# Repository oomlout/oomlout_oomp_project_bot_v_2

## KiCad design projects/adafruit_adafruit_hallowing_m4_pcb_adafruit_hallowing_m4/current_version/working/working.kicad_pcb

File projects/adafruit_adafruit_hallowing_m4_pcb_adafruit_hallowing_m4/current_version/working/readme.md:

# adafruit_hallowing_m4_pcb
 
## summary 
* id: adafruit_adafruit_hallowing_m4_pcb_adafruit_hallowing_m4
* user: adafruit
* name: adafruit_hallowing_m4_pcb
* board: adafruit_hallowing_m4
* repo: https://github.com/adafruit/Adafruit-Hallowing-M4-PCB

* src_file_repo_sch: 
* src_file_repo_sch_link: https://github.com/adafruit/Adafruit-Hallowing-M4-PCB/tree/master/
* full details link: https://github.com/oomlout/oomlout_oomp_project_bot_v_2/tree/main/projects/adafruit_adafruit_hallowing_m4_pcb_adafruit_hallowing_m4/current_version/working  

## schematic  
  
[schematic (pdf)](working_schematic.pdf) 

## pcb  

[board (pdf)](working.pdf)  

## working_bom
| Id | Designator | Footprint | Quantity | Designation | Supplier and ref |  | None | 
| --- | --- | --- | --- | --- | --- | --- | --- | 
| 1 | @HOLE0,@HOLE2,@HOLE3,@HOLE1 |  | 4 |  |  |  | [''] | 
| 2 | C28,C23,C32,C29,C12,C27,C24 | 0603-NO | 7 | 1uF |  |  | [''] | 
| 3 | C18,C30,C21,C26,C19 | 0805-NO | 5 | 10uF |  |  | [''] | 
| 4 | TP3,TP29 | PCB_ALLI_LONG | 2 | SEWTAP_ALLILONG |  |  | [''] | 
| 5 | TP6,TP7 | TESTPOINT_ROUND_1.5MM | 2 |  |  |  | [''] | 
| 6 | U$32,U$31 | MOUNTINGHOLE_2.5_PLATED | 2 | MOUNTINGHOLE2.5 |  |  | [''] | 
| 7 | U$59 | 53398-0271 | 1 | CON_MOLEX_2P |  |  | [''] | 
| 8 | R5,R2,R1,R4 | 0603-NO | 4 | 1M |  |  | [''] | 
| 9 | U$1 | HALLOWINGM4_BACK | 1 |  |  |  | [''] | 
| 10 | C31,C25 | 0603-NO | 2 | 0.1uF |  |  | [''] | 
| 11 | R25,R26 | 0603-NO | 2 | 100K |  |  | [''] | 
| 12 | CHG1 | CHIPLED_0805_NOOUTLINE | 1 | ORANGE |  |  | [''] | 
| 13 | L1 | CHIPLED_0805_NOOUTLINE | 1 | RED |  |  | [''] | 
| 14 | SW3 | BTN_KMR2_4.6X2.8 | 1 | SPST_TACT-EVQQ2 |  |  | [''] | 
| 15 | R11,R17,R18 | 0603-NO | 3 | 1K |  |  | [''] | 
| 16 | R24 | 0603-NO | 1 | 47K |  |  | [''] | 
| 17 | C33,C22,C16,C17 | 0805-NO | 4 | 10ÂµF |  |  | [''] | 
| 18 | R23 | 0603-NO | 1 | 10 |  |  | [''] | 
| 19 | Q6,Q5 | SOT23-R | 2 | DMG3405 |  |  | [''] | 
| 20 | LED3,LED2,LED4,LED1 | WS2812B_4020 | 4 | WS2812B_4020 |  |  | [''] | 
| 21 | R19,R3,R20 | 0603-NO | 3 | 10K |  |  | [''] | 
| 22 | U7 | SOT23-5 | 1 | MCP73831T-2ACI/OT |  |  | [''] | 
| 23 | U9 | SOIC8_208MIL | 1 | GD25Q64 |  |  | [''] | 
| 24 | U$34,U$35 | FIDUCIAL_1MM | 2 | FIDUCIAL_1MM |  |  | [''] | 
| 25 | MS2 | FEATHERWING_SMT_NOHOLES | 1 | FEATHERWING_SMTDUALNOHOLES |  |  | [''] | 
| 26 | TP28,TP4 | PCB_ALLI | 2 | SEWTAPPCB_ALLIGATOR |  |  | [''] | 
| 27 | U4 | ALS-PT26-21C | 1 | ALS-PT21 |  |  | [''] | 
| 28 | IC3 | SOT23-6 | 1 | PAM8301 |  |  | [''] | 
| 29 | R27 | RESPACK_4X0603 | 1 | 10K |  |  | [''] | 
| 30 | Q7 | SOT363 | 1 | BSS138 |  |  | [''] | 
| 31 | Q4 | SOT23-WIDE | 1 | BSS138 |  |  | [''] | 
| 32 | I2C1 | JSTPH4 | 1 | JST PH 4 |  |  | [''] | 
| 33 | SJ2 | SOLDERJUMPER_2WAY_OPEN_NOPASTE | 1 |  |  |  | [''] | 
| 34 | U6 | SOT23-5 | 1 | AP2112-3.3 |  |  | [''] | 
| 35 | D6,D5 | SOD-323 | 2 | 3.6V |  |  | [''] | 
| 36 | FB1 | 0805-NO | 1 | Ferrite |  |  | [''] | 
| 37 | R14 | 0603-NO | 1 | 4.7K |  |  | [''] | 
| 38 | IC2 | LGA12_2X2MM | 1 | MSA301 |  |  | [''] | 
| 39 | R10 | 0603-NO | 1 | 2.2K |  |  | [''] | 
| 40 | NEOPIX1,SENSE1 | JSTPH3 | 2 | JST PH 3 |  |  | [''] | 
| 41 | D3 | SOD-123 | 1 | MBR0540 |  |  | [''] | 
| 42 | U$63 | PQFN64-1 | 1 | ATSAMD51J19 |  |  | [''] | 
| 43 | SW1 | EG1390 | 1 |  |  |  | [''] | 
| 44 | R15 | RESPACK_4X0603 | 1 | 100K |  |  | [''] | 
| 45 | X2 | 4UCONN_20329_V2 | 1 | microUSB |  |  | [''] | 
| 46 | X4 | JSTPH2 | 1 | JSTPH |  |  | [''] | 
| 47 | U$79 | PCBFEAT-REV-040 | 1 |  |  |  | [''] | 
| 48 | TFT1 | TFT_1.54IN_240X240_HANDSOLDER | 1 | DISP_LCD_GENERIC_SPITFT_VDDIO_1.54_240X240_HANDSOLDER |  |  | [''] | 
| 49 | U$2 | HALLOWINGM4_FRONT | 1 |  |  |  | [''] | 

## bom_schematic
| Ref | Qnty | Value | Cmp name | Footprint | Description | Vendor | DNP | 
| --- | --- | --- | --- | --- | --- | --- | --- | 
| C12, C23, C24, C27, C28, C29, C32 | 7 | 1uF | CAP_CERAMIC0603_NO | working:0603-NO |  |  |  | 
| C16, C17, C22, C33 | 4 | 10ÂµF | CAP_CERAMIC0805-NOOUTLINE | working:0805-NO |  |  |  | 
| C18, C19, C21, C26, C30 | 5 | 10uF | CAP_CERAMIC0805-NOOUTLINE | working:0805-NO |  |  |  | 
| C25, C31 | 2 | 0.1uF | CAP_CERAMIC0603_NO | working:0603-NO |  |  |  | 
| CHG1 | 1 | ORANGE | LED0805_NOOUTLINE | working:CHIPLED_0805_NOOUTLINE |  |  |  | 
| D3 | 1 | MBR0540 | DIODE-SCHOTTKYSOD-123 | working:SOD-123 |  |  |  | 
| D5, D6 | 2 | 3.6V | DIODE-ZENERSOD323 | working:SOD-323 |  |  |  | 
| FB1 | 1 | Ferrite | FERRITE-0805NO | working:0805-NO |  |  |  | 
| I2C1 | 1 | STEMMA_I2C_RASMT | STEMMA_I2C_RASMT | working:JSTPH4 |  |  |  | 
| IC2 | 1 | MSA301 | MSA301 | working:LGA12_2X2MM |  |  |  | 
| IC3 | 1 | PAM8301 | PAM8301 | working:SOT23-6 |  |  |  | 
| L1 | 1 | RED | LED0805_NOOUTLINE | working:CHIPLED_0805_NOOUTLINE |  |  |  | 
| LED1, LED2, LED3, LED4 | 4 | WS2812B_4020 | WS2812B_4020 | working:WS2812B_4020 |  |  |  | 
| MS2 | 1 | FEATHERWING_SMTDUALNOHOLES | FEATHERWING_SMTDUALNOHOLES | working:FEATHERWING_SMT_NOHOLES |  |  |  | 
| NEOPIX1 | 1 | JST PH 3 | CON_JST_PH_3PIN | working:JSTPH3 |  |  |  | 
| Q4 | 1 | BSS138 | MOSFET-NWIDE | working:SOT23-WIDE |  |  |  | 
| Q5, Q6 | 2 | DMG3405 | MOSFET-P | working:SOT23-R |  |  |  | 
| Q7 | 1 | BSS138 | MOSFET-N_DUAL | working:SOT363 |  |  |  | 
| R1, R2, R4, R5 | 4 | 1M | RESISTOR_0603_NOOUT | working:0603-NO |  |  |  | 
| R3, R19, R20 | 3 | 10K | RESISTOR_0603_NOOUT | working:0603-NO |  |  |  | 
| R10 | 1 | 2.2K | RESISTOR_0603_NOOUT | working:0603-NO |  |  |  | 
| R11, R17, R18 | 3 | 1K | RESISTOR_0603_NOOUT | working:0603-NO |  |  |  | 
| R14 | 1 | 4.7K | RESISTOR_0603_NOOUT | working:0603-NO |  |  |  | 
| R15 | 1 | 100K | RESISTOR_4PACK | working:RESPACK_4X0603 |  |  |  | 
| R23 | 1 | 10 | RESISTOR_0603_NOOUT | working:0603-NO |  |  |  | 
| R24 | 1 | 47K | RESISTOR_0603_NOOUT | working:0603-NO |  |  |  | 
| R25, R26 | 2 | 100K | RESISTOR_0603_NOOUT | working:0603-NO |  |  |  | 
| R27 | 1 | 10K | RESISTOR_4PACK | working:RESPACK_4X0603 |  |  |  | 
| SENSE1 | 1 | JST PH 3 | CON_JST_PH_3PIN | working:JSTPH3 |  |  |  | 
| SJ2 | 1 | SOLDERJUMPER_2WAY | SOLDERJUMPER_2WAY | working:SOLDERJUMPER_2WAY_OPEN_NOPASTE |  |  |  | 
| SW1 | 1 | SWITCH_DPDTEG1390 | SWITCH_DPDTEG1390 | working:EG1390 |  |  |  | 
| SW3 | 1 | SPST_TACT-EVQQ2 | SWITCH_TACT_SMT4.6X2.8 | working:BTN_KMR2_4.6X2.8 |  |  |  | 
| TFT1 | 1 | DISP_LCD_GENERIC_SPITFT_VDDIO_1.54_240X240_HANDSOLDER | DISP_LCD_GENERIC_SPITFT_VDDIO_1.54_240X240_HANDSOLDER | working:TFT_1.54IN_240X240_HANDSOLDER |  |  |  | 
| TP3, TP29 | 2 | SEWTAP_ALLILONG | SEWTAP_ALLILONG | working:PCB_ALLI_LONG |  |  |  | 
| TP4, TP28 | 2 | SEWTAPPCB_ALLIGATOR | SEWTAPPCB_ALLIGATOR | working:PCB_ALLI |  |  |  | 
| TP6, TP7 | 2 | TESTPOINTROUND1.5MM | TESTPOINTROUND1.5MM | working:TESTPOINT_ROUND_1.5MM |  |  |  | 
| U4 | 1 | ALS-PT21 | PHOTOTRANSISTOR_PT26-21C | working:ALS-PT26-21C |  |  |  | 
| U6 | 1 | AP2112-3.3 | VREG_SOT23-5 | working:SOT23-5 |  |  |  | 
| U7 | 1 | MCP73831T-2ACI/OT | MCP73831/2 | working:SOT23-5 |  |  |  | 
| U9 | 1 | GD25Q64 | SPIFLASH_8PIN208MIL | working:SOIC8_208MIL |  |  |  | 
| U$31, U$32 | 2 | MOUNTINGHOLE2.5 | MOUNTINGHOLE2.5 | working:MOUNTINGHOLE_2.5_PLATED |  |  |  | 
| U$34, U$35 | 2 | FIDUCIAL_1MM | FIDUCIAL_1MM | working:FIDUCIAL_1MM |  |  |  | 
| U$59 | 1 | CON_MOLEX_2P | CON_MOLEX_2P | working:53398-0271 |  |  |  | 
| U$63 | 1 | ATSAMD51J | ATSAMD51J | working:PQFN64-1 |  |  |  | 
| X2 | 1 | microUSB | USB_MICRO_20329_V2 | working:4UCONN_20329_V2 |  |  |  | 
| X4 | 1 | JSTPH | CON_JST_PH_2PIN | working:JSTPH2 |  |  |  | 

## mounting_holes
| x | y | package | value | ref | size | 
| --- | --- | --- | --- | --- | --- | 
| 17.78 | 0.0 | MOUNTINGHOLE_2.5_PLATED | MOUNTINGHOLE2.5 | U$31 | m3 | 
| 0.0 | 0.0 | MOUNTINGHOLE_2.5_PLATED | MOUNTINGHOLE2.5 | U$32 | m3 |

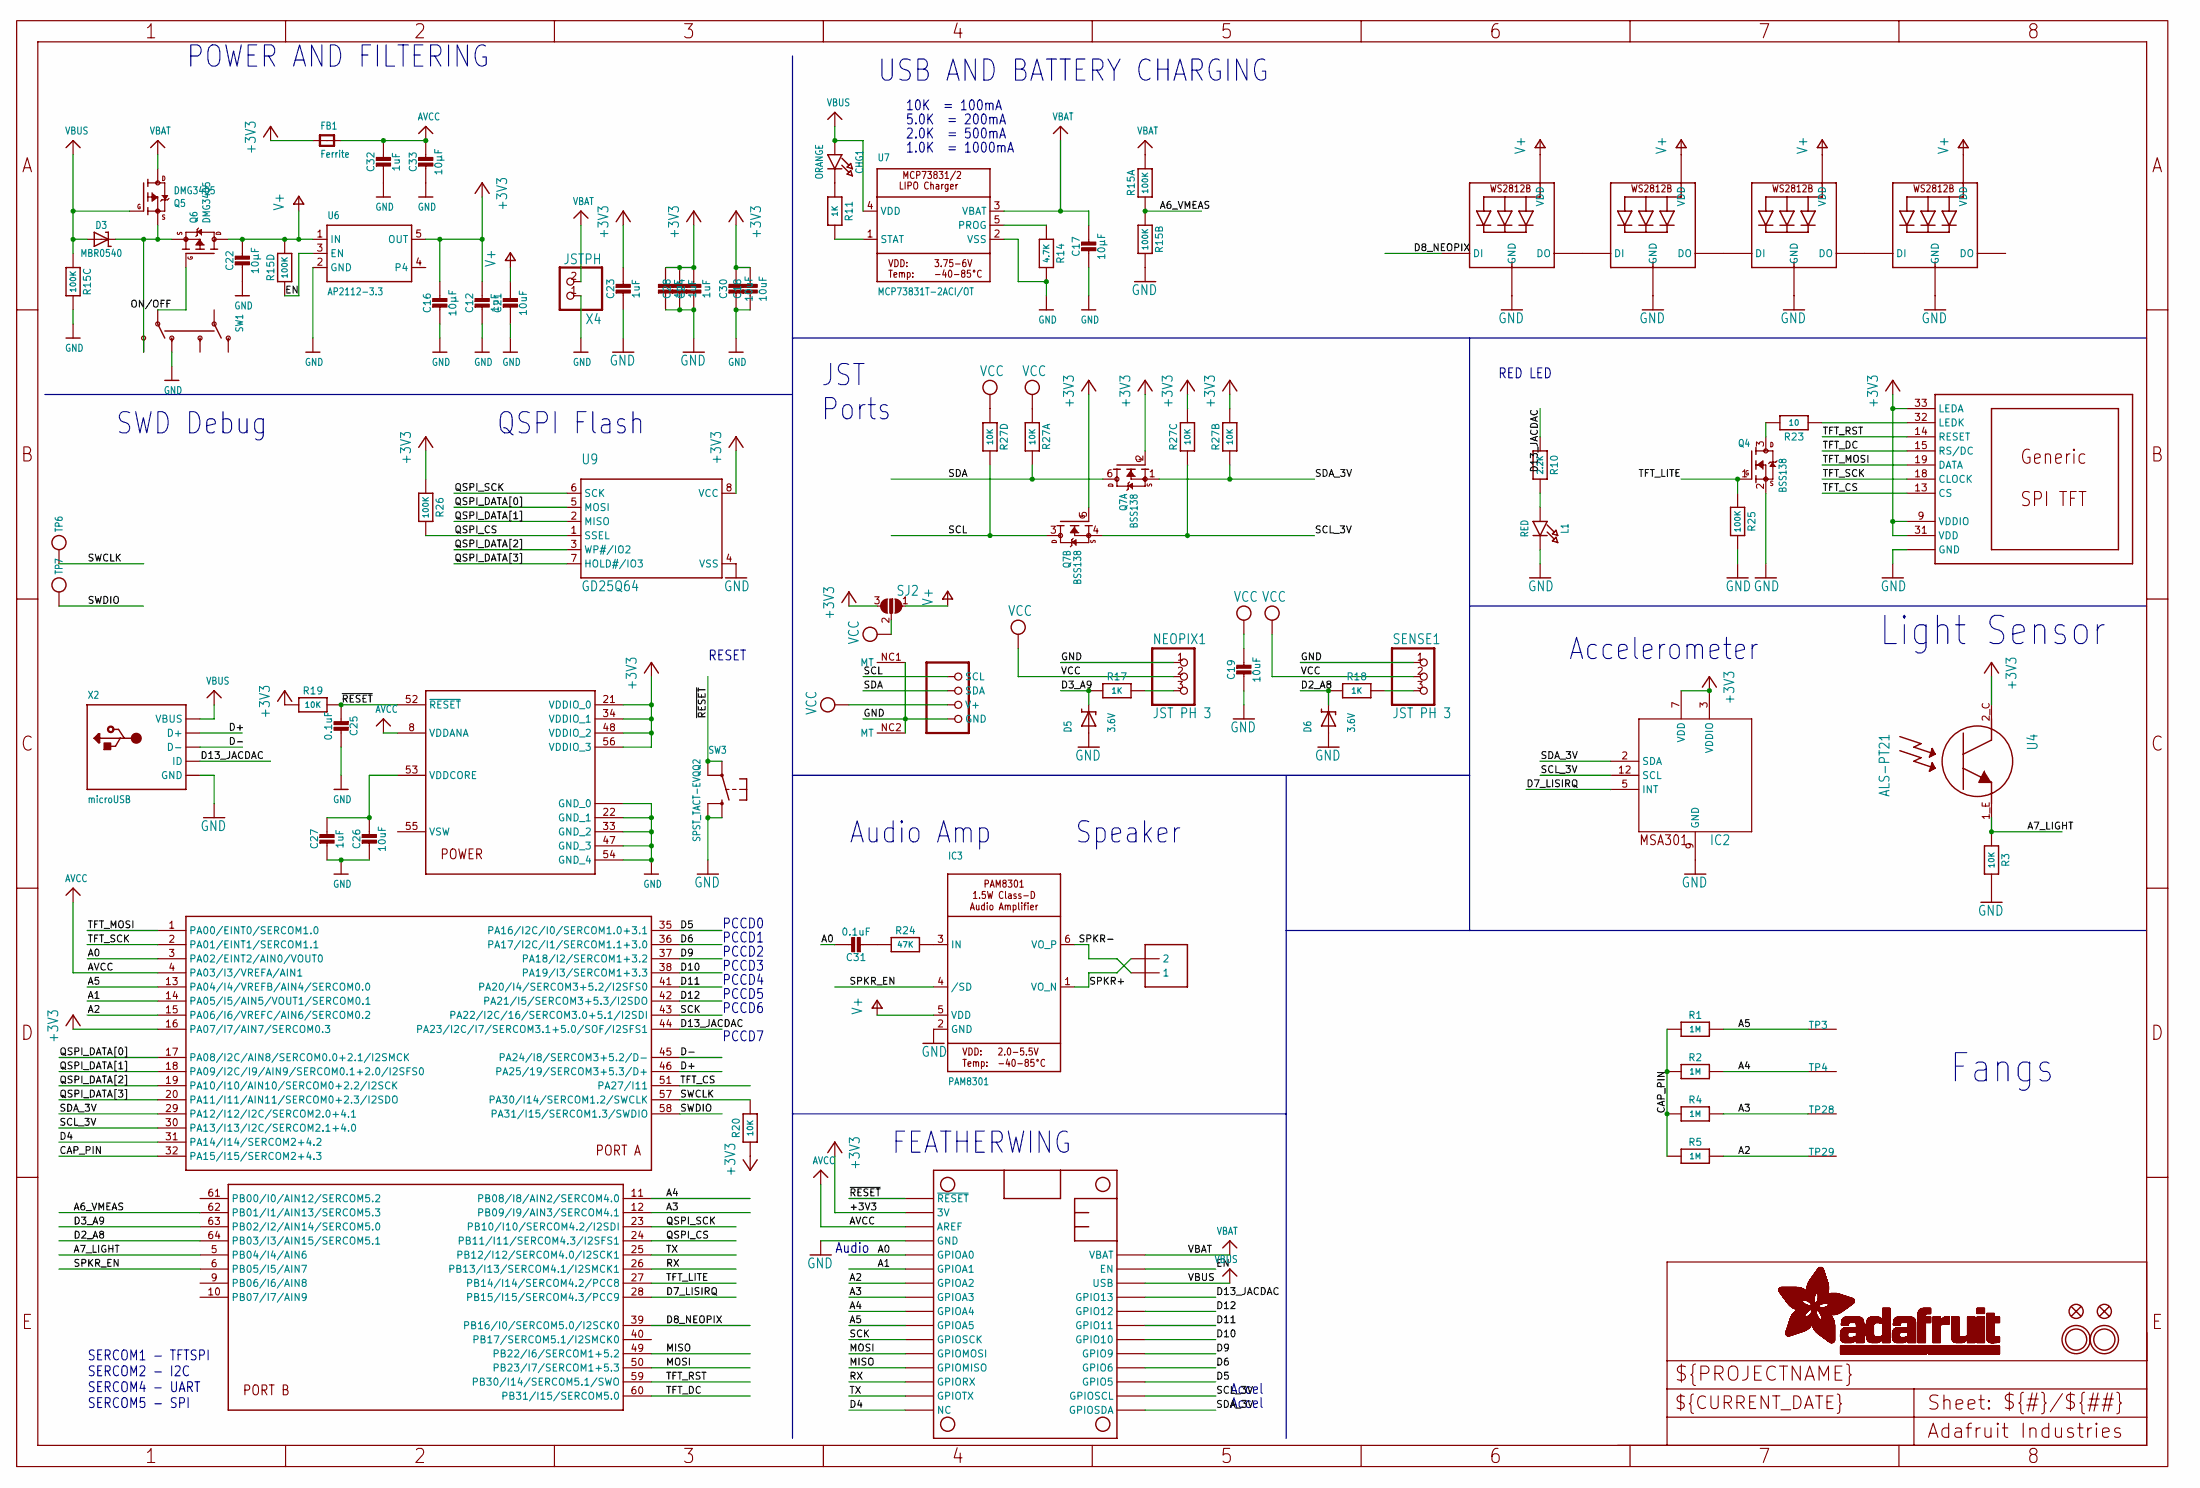
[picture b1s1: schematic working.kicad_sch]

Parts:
C12, C23, C24, C27, C28, C29, C32: 1uF; 0603-NO
C16, C17, C22, C33: 10µF; 0805-NO
C18, C19, C21, C26, C30: 10uF; 0805-NO
C25, C31: 0.1uF; 0603-NO
CHG1: ORANGE; CHIPLED_0805_NOOUTLINE
D3: MBR0540; SOD-123
D5, D6: 3.6V; SOD-323
FB1: Ferrite; 0805-NO
I2C1: STEMMA_I2C_RASMT; JSTPH4
IC2: MSA301; LGA12_2X2MM
IC3: PAM8301; SOT23-6
L1: RED; CHIPLED_0805_NOOUTLINE
LED1, LED2, LED3, LED4: WS2812B_4020
MS2: FEATHERWING_SMTDUALNOHOLES; FEATHERWING_SMT_NOHOLES
NEOPIX1: JST PH 3; JSTPH3
Q4: BSS138; SOT23-WIDE
Q5, Q6: DMG3405; SOT23-R
Q7: BSS138; SOT363
R1, R2, R4, R5: 1M; 0603-NO
R3, R19, R20: 10K; 0603-NO
R10: 2.2K; 0603-NO
R11, R17, R18: 1K; 0603-NO
R14: 4.7K; 0603-NO
R15: 100K; RESPACK_4X0603
R23: 10; 0603-NO
R24: 47K; 0603-NO
R25, R26: 100K; 0603-NO
R27: 10K; RESPACK_4X0603
SENSE1: JST PH 3; JSTPH3
SJ2: SOLDERJUMPER_2WAY; SOLDERJUMPER_2WAY_OPEN_NOPASTE
SW1: SWITCH_DPDTEG1390; EG1390
SW3: SPST_TACT-EVQQ2; BTN_KMR2_4.6X2.8
TFT1: DISP_LCD_GENERIC_SPITFT_VDDIO_1.54_240X240_HANDSO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; TFT_1.54IN_240X240_HANDSOLDER
TP3, TP29: SEWTAP_ALLILONG; PCB_ALLI_LONG
TP4, TP28: SEWTAPPCB_ALLIGATOR; PCB_ALLI
TP6, TP7: TESTPOINTROUND1.5MM; TESTPOINT_ROUND_1.5MM
U4: ALS-PT21; ALS-PT26-21C
U6: AP2112-3.3; SOT23-5
U7: MCP73831T-2ACI/OT; SOT23-5
U9: GD25Q64; SOIC8_208MIL
U$31, U$32: MOUNTINGHOLE2.5; MOUNTINGHOLE_2.5_PLATED
U$34, U$35: FIDUCIAL_1MM
U$59: CON_MOLEX_2P; 53398-0271
U$63: ATSAMD51J; PQFN64-1
X2: microUSB; 4UCONN_20329_V2
X4: JSTPH; JSTPH2

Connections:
+3V3: C12.1, C16.1, C18.1, C23.1, C24.1, C28.1, C29.1, C30.1, FB1.1, IC2.3 (VDDIO), IC2.7 (VDD), MS2.2 (3V), MS2.2B (3V), Q7.2 (G), Q7.5 (G), R19.1, R20.1, R26.1, R27.2 (1), R27.3 (1), SJ2.3, TFT1.9 (VDDIO), TFT1.31 (VDD), TFT1.33 (LEDA), U4.2_C (C), U6.5 (OUT), U9.8 (VCC), U$63.16 (PA07/I7/AIN7/SERCOM0.3), U$63.21 (VDDIO_0), U$63.34 (VDDIO_1), U$63.48 (VDDIO_2), U$63.56 (VDDIO_3)
A0: C31.1, MS2.5 (GPIOA0), MS2.5B (GPIOA0), U$63.3 (PA02/EINT2/AIN0/VOUT0)
A1: MS2.6 (GPIOA1), MS2.6B (GPIOA1), U$63.14 (PA05/I5/AIN5/VOUT1/SERCOM0.1)
A2: MS2.7 (GPIOA2), MS2.7B (GPIOA2), R5.1, TP29.P$1, U$63.15 (PA06/I6/VREFC/AIN6/SERCOM0.2)
A3: MS2.8 (GPIOA3), MS2.8B (GPIOA3), R4.1, TP28.P$1, U$63.12 (PB09/I9/AIN3/SERCOM4.1)
A4: MS2.9 (GPIOA4), MS2.9B (GPIOA4), R2.1, TP4.P$1, U$63.11 (PB08/I8/AIN2/SERCOM4.0)
A5: MS2.10 (GPIOA5), MS2.10B (GPIOA5), R1.1, TP3.P$1, U$63.13 (PA04/I4/VREFB/AIN4/SERCOM0.0)
A6_VMEAS: R15.1, R15.2 (1), U$63.62 (PB01/I1/AIN13/SERCOM5.3)
A7_LIGHT: R3.2, U4.1_E (E), U$63.5 (PB04/I4/AIN6)
AVCC: C32.1, C33.1, FB1.2, MS2.3 (AREF), MS2.3B (AREF), U$63.4 (PA03/I3/VREFA/AIN1), U$63.8 (VDDANA)
CAP_PIN: R1.2, R2.2, R4.2, R5.2, U$63.32 (PA15/I15/SERCOM2+4.3)
CHG_LED1: R11.2, U7.1 (STAT)
CHG_RATE1: R14.1, U7.5 (PROG)
D2: R18.1, SENSE1.3
D2_A8: D6.C, R18.2, U$63.64 (PB03/I3/AIN15/SERCOM5.1)
D3: NEOPIX1.3, R17.1
D3_A9: D5.C, R17.2, U$63.63 (PB02/I2/AIN14/SERCOM5.0)
D4: MS2.16 (NC), MS2.16B (NC), U$63.31 (PA14/I14/SERCOM2+4.2)
D5: MS2.19 (GPIO5), MS2.19B (GPIO5), U$63.35 (PA16/I2C/I0/SERCOM1.0+3.1)
D6: MS2.20 (GPIO6), MS2.20B (GPIO6), U$63.36 (PA17/I2C/I1/SERCOM1.1+3.0)
D7_LISIRQ: IC2.5 (INT), U$63.28 (PB15/I15/SERCOM4.3/PCC9)
D8_NEOPIX: LED2.1 (DI), U$63.39 (PB16/I0/SERCOM5.0/I2SCK0)
D9: MS2.21 (GPIO9), MS2.21B (GPIO9), U$63.37 (PA18/I2/SERCOM1+3.2)
D10: MS2.22 (GPIO10), MS2.22B (GPIO10), U$63.38 (PA19/I3/SERCOM1+3.3)
D11: MS2.23 (GPIO11), MS2.23B (GPIO11), U$63.41 (PA20/I4/SERCOM3+5.2/I2SFS0)
D12: MS2.24 (GPIO12), MS2.24B (GPIO12), U$63.42 (PA21/I5/SERCOM3+5.3/I2SDO)
D13_JACDAC: MS2.25 (GPIO13), MS2.25B (GPIO13), R10.1, U$63.44 (PA23/I2C/I7/SERCOM3.1+5.0/SOF/I2SFS1), X2.ID
D+: U$63.46 (PA25/19/SERCOM3+5.3/D+), X2.D+
D-: U$63.45 (PA24/I8/SERCOM3+5.2/D-), X2.D-
EN: MS2.27 (EN), MS2.27B (EN), R15.4 (1), U6.3 (EN)
GND: C12.2, C16.2, C17.2, C18.2, C19.2, C21.2, C22.2, C23.2, C24.2, C25.1, C26.2, C27.2, C28.2, C29.2, C30.2, C32.2, C33.2, D5.A, D6.A, I2C1.1 (GND), I2C1.NC1 (MT), I2C1.NC2 (MT), IC2.9 (GND), IC3.2 (GND), L1.C, LED1.4 (GND), LED2.4 (GND), LED3.4 (GND), LED4.4 (GND), MS2.4 (GND), MS2.4B (GND), NEOPIX1.1, Q4.2 (S), R3.1, R14.2, R15.6 (2), R15.7 (2), R25.2, SENSE1.1, SW1.O2, SW3.B (S), SW3.B' (S1), TFT1.8 (GND), TFT1.21 (GND), TFT1.22 (GND), U6.2 (GND), U7.2 (VSS), U9.4 (VSS), U$63.7 (GND_0), U$63.22 (GND_1), U$63.33 (GND_2), U$63.47 (GND_3), U$63.54 (GND_4), U$63.EXP (GND_0), X2.BASE@1 (GND), X2.BASE@2 (GND), X2.GND, X2.SPRT@1 (GND), X2.SPRT@2 (GND), X2.SPRT@3 (GND), X2.SPRT@4 (GND), X4.1
MISO: MS2.13 (GPIOMISO), MS2.13B (GPIOMISO), U$63.49 (PB22/I6/SERCOM1+5.2)
MOSI: MS2.12 (GPIOMOSI), MS2.12B (GPIOMOSI), U$63.50 (PB23/I7/SERCOM1+5.3)
unnamed: R23.1, TFT1.32 (LEDK)
unnamed: L1.A, R10.2
unnamed: CHG1.C, R11.1
unnamed: D3.C, Q5.2 (S), Q6.2 (S), SW1.S2
unnamed: LED1.1 (DI), LED2.3 (DO)
unnamed: LED1.3 (DO), LED3.1 (DI)
unnamed: LED3.3 (DO), LED4.1 (DI)
unnamed: Q4.3 (D), R23.2
unnamed: C31.2, R24.1
unnamed: IC3.3 (IN), R24.2
ON/OFF: Q6.1 (G), SW1.P2
QSPI_CS: R26.2, U9.1 (SSEL), U$63.24 (PB11/I11/SERCOM4.3/I2SFS1)
QSPI_DATA[0]: U9.5 (MOSI), U$63.17 (PA08/I2C/AIN8/SERCOM0.0+2.1/I2SMCK)
QSPI_DATA[1]: U9.2 (MISO), U$63.18 (PA09/I2C/I9/AIN9/SERCOM0.1+2.0/I2SFS0)
QSPI_DATA[2]: U9.3 (WP#/IO2), U$63.19 (PA10/I10/AIN10/SERCOM0+2.2/I2SCK)
QSPI_DATA[3]: U9.7 (HOLD#/IO3), U$63.20 (PA11/I11/AIN11/SERCOM0+2.3/I2SDO)
QSPI_SCK: U9.6 (SCK), U$63.23 (PB10/I10/SERCOM4.2/I2SDI)
RX: MS2.14 (GPIORX), MS2.14B (GPIORX), U$63.26 (PB13/I13/SERCOM4.1/I2SMCK1)
SCK: MS2.11 (GPIOSCK), MS2.11B (GPIOSCK), U$63.43 (PA22/I2C/16/SERCOM3.0+5.1/I2SDI)
SCL: I2C1.4 (SCL), Q7.3 (D), R27.5 (2)
SCL_3V: IC2.12 (SCL), MS2.18 (GPIOSCL), MS2.18B (GPIOSCL), Q7.4 (S), R27.6 (2), U$63.30 (PA13/I13/I2C/SERCOM2.1+4.0)
SDA: I2C1.3 (SDA), Q7.6 (D), R27.8 (2)
SDA_3V: IC2.2 (SDA), MS2.17 (GPIOSDA), MS2.17B (GPIOSDA), Q7.1 (S), R27.7 (2), U$63.29 (PA12/I12/I2C/SERCOM2.0+4.1)
SPKR+: IC3.1 (VO_N), U$59.2
SPKR-: IC3.6 (VO_P), U$59.1
SPKR_EN: IC3.4 (/SD), U$63.6 (PB05/I5/AIN7)
SWCLK: R20.2, TP6.P$1, U$63.57 (PA30/I14/SERCOM1.2/SWCLK)
SWDIO: TP7.P$1, U$63.58 (PA31/I15/SERCOM1.3/SWDIO)
TFT_CS: TFT1.13 (CS), U$63.51 (PA27/I11)
TFT_DC: TFT1.15 (RS/DC), U$63.60 (PB31/I15/SERCOM5.0)
TFT_LITE: Q4.1 (G), R25.1, U$63.27 (PB14/I14/SERCOM4.2/PCC8)
TFT_MOSI: TFT1.19 (DATA), U$63.1 (PA00/EINT0/SERCOM1.0)
TFT_RST: TFT1.14 (RESET), U$63.59 (PB30/I14/SERCOM5.1/SWO)
TFT_SCK: TFT1.18 (CLOCK), U$63.2 (PA01/EINT1/SERCOM1.1)
TX: MS2.15 (GPIOTX), MS2.15B (GPIOTX), U$63.25 (PB12/I12/SERCOM4.0/I2SCK1)
V+: C21.1, C22.1, IC3.5 (VDD), LED1.2 (VDD), LED2.2 (VDD), LED3.2 (VDD), LED4.2 (VDD), Q6.3 (D), R15.5 (2), SJ2.1, U6.1 (IN)
VBAT: C17.1, MS2.28 (VBAT), MS2.28B (VBAT), Q5.3 (D), R15.8 (2), U7.3 (VBAT), X4.2
VBUS: CHG1.A, D3.A, MS2.26 (USB), MS2.26B (USB), Q5.1 (G), R15.3 (1), U7.4 (VDD), X2.VBUS
VCC: C19.1, I2C1.2 (V+), NEOPIX1.2, R27.1, R27.4 (1), SENSE1.2, SJ2.2
VDDCORE2: C26.1, C27.1, U$63.53 (VDDCORE)
~RESET: C25.2, MS2.1 (~RESET), MS2.1B (~RESET), R19.2, SW3.A, SW3.A' (P1), U$63.52 (~RESET)

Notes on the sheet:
PCCD2
Audio Amp
2.0K = 500mA
1.0K = 1000mA
RESET
PCCD7
Audio
SWD Debug
PCCD4
USB AND BATTERY CHARGING
Fangs
Accel
QSPI Flash
Accelerometer
10K = 100mA
5.0K = 200mA
Speaker
SERCOM1 - TFTSPI SERCOM2 - I2C SERCOM4 - UART SERCOM5 - SPI
PCCD1
PCCD5
PCCD3
Light Sensor
POWER AND FILTERING
FEATHERWING
PCCD0
JST Ports
RED LED
PCCD6

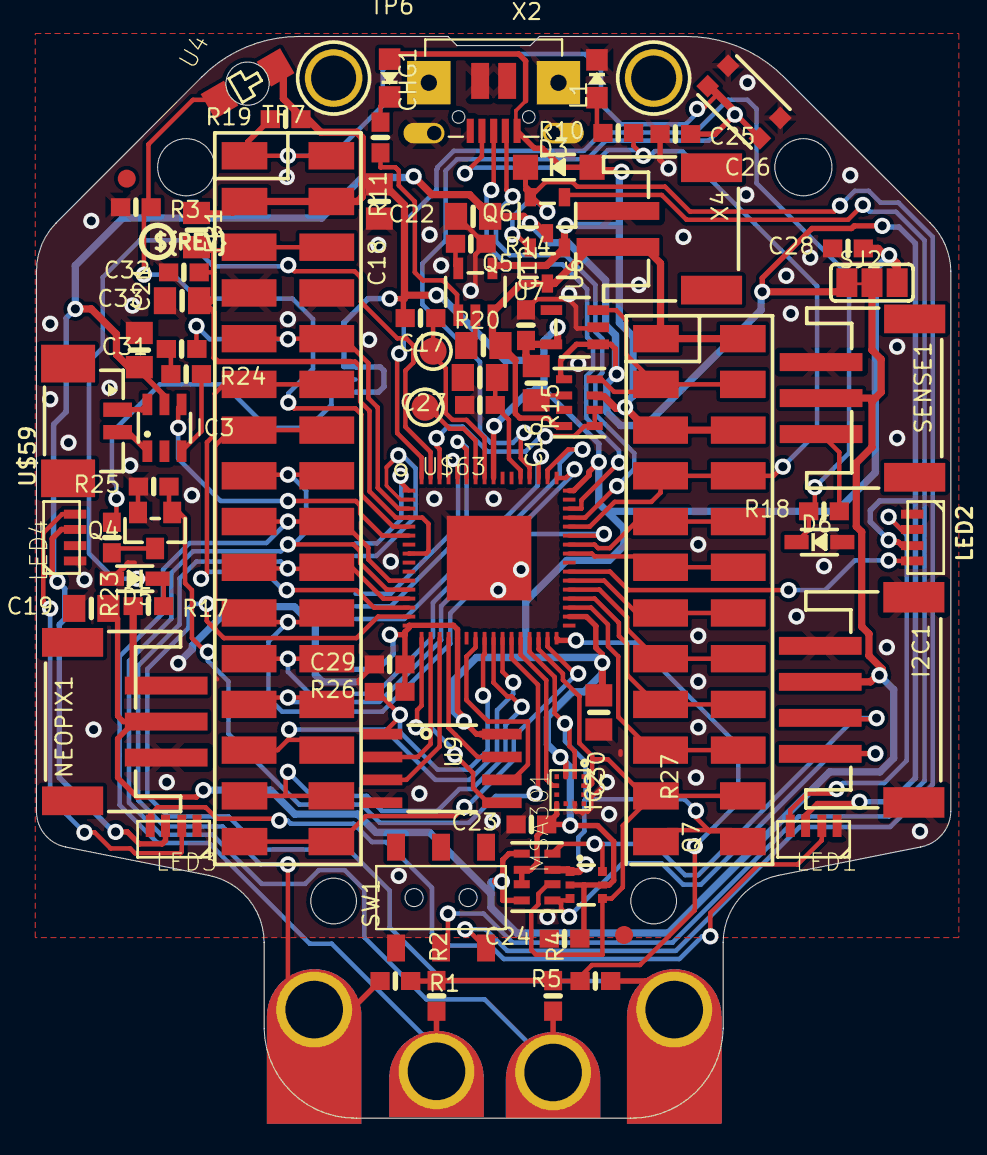
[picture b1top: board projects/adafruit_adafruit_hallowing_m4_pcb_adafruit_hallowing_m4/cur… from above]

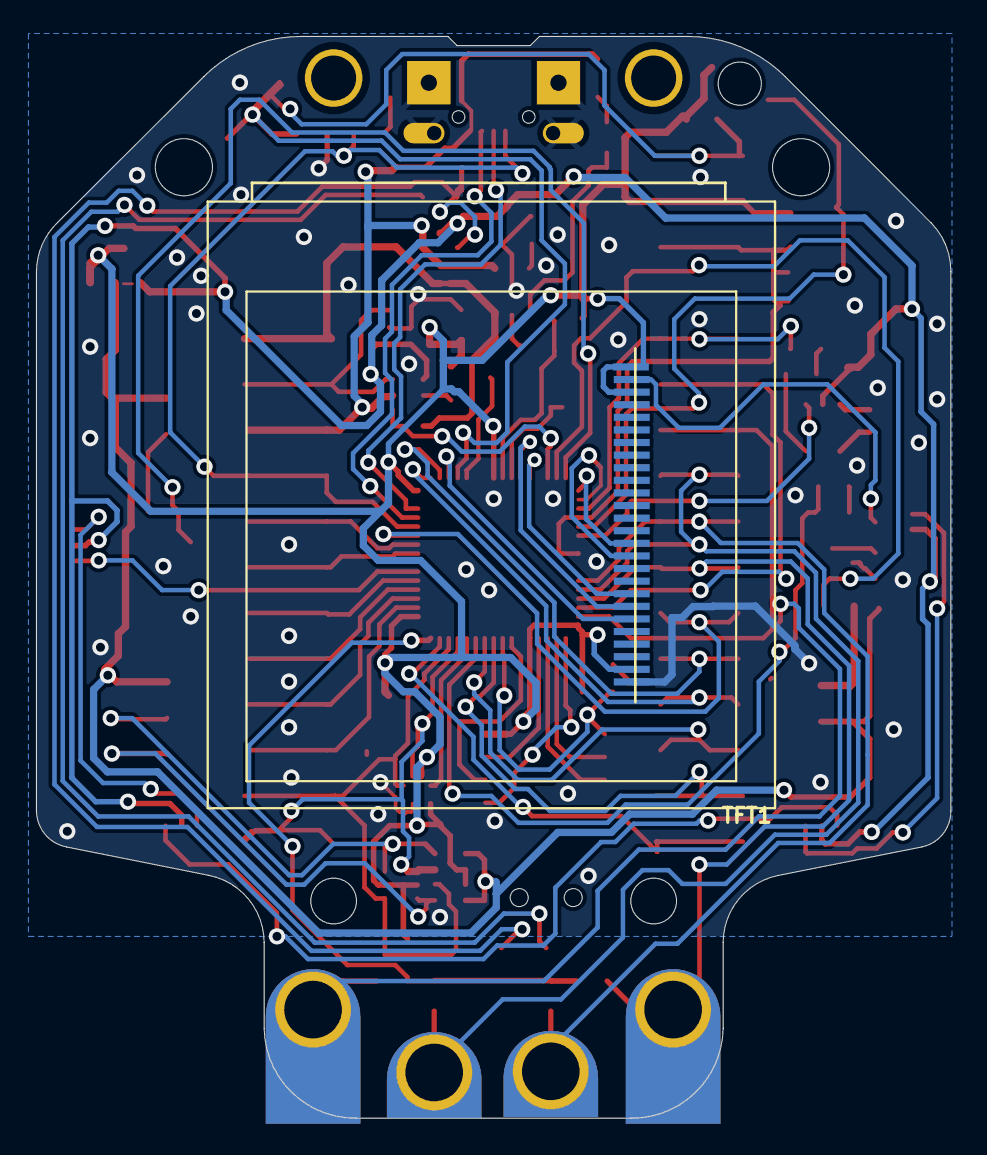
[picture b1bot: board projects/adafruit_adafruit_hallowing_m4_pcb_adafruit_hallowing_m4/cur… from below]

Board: 2 copper layers, 50.8 x 60.1 mm, 85 parts (2 on the bottom side), 74 nets.

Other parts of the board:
@HOLE0, @HOLE1, @HOLE2, @HOLE3: (no value)
U$1: HALLOWINGM4_BACK
U$2: HALLOWINGM4_FRONT
U$79: PCBFEAT-REV-040

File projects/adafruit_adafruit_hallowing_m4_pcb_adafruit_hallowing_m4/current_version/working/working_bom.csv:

"Id";"Designator";"Footprint";"Quantity";"Designation";"Supplier and ref";
1;"@HOLE0,@HOLE2,@HOLE3,@HOLE1";"";4;"";;;
2;"C28,C23,C32,C29,C12,C27,C24";"0603-NO";7;"1uF";;;
3;"C18,C30,C21,C26,C19";"0805-NO";5;"10uF";;;
4;"TP3,TP29";"PCB_ALLI_LONG";2;"SEWTAP_ALLILONG";;;
5;"TP6,TP7";"TESTPOINT_ROUND_1.5MM";2;"";;;
6;"U$32,U$31";"MOUNTINGHOLE_2.5_PLATED";2;"MOUNTINGHOLE2.5";;;
7;"U$59";"53398-0271";1;"CON_MOLEX_2P";;;
8;"R5,R2,R1,R4";"0603-NO";4;"1M";;;
9;"U$1";"HALLOWINGM4_BACK";1;"";;;
10;"C31,C25";"0603-NO";2;"0.1uF";;;
11;"R25,R26";"0603-NO";2;"100K";;;
12;"CHG1";"CHIPLED_0805_NOOUTLINE";1;"ORANGE";;;
13;"L1";"CHIPLED_0805_NOOUTLINE";1;"RED";;;
14;"SW3";"BTN_KMR2_4.6X2.8";1;"SPST_TACT-EVQQ2";;;
15;"R11,R17,R18";"0603-NO";3;"1K";;;
16;"R24";"0603-NO";1;"47K";;;
17;"C33,C22,C16,C17";"0805-NO";4;"10µF";;;
18;"R23";"0603-NO";1;"10";;;
19;"Q6,Q5";"SOT23-R";2;"DMG3405";;;
20;"LED3,LED2,LED4,LED1";"WS2812B_4020";4;"WS2812B_4020";;;
21;"R19,R3,R20";"0603-NO";3;"10K";;;
22;"U7";"SOT23-5";1;"MCP73831T-2ACI/OT";;;
23;"U9";"SOIC8_208MIL";1;"GD25Q64";;;
24;"U$34,U$35";"FIDUCIAL_1MM";2;"FIDUCIAL_1MM";;;
25;"MS2";"FEATHERWING_SMT_NOHOLES";1;"FEATHERWING_SMTDUALNOHOLES";;;
26;"TP28,TP4";"PCB_ALLI";2;"SEWTAPPCB_ALLIGATOR";;;
27;"U4";"ALS-PT26-21C";1;"ALS-PT21";;;
28;"IC3";"SOT23-6";1;"PAM8301";;;
29;"R27";"RESPACK_4X0603";1;"10K";;;
30;"Q7";"SOT363";1;"BSS138";;;
31;"Q4";"SOT23-WIDE";1;"BSS138";;;
32;"I2C1";"JSTPH4";1;"JST PH 4";;;
33;"SJ2";"SOLDERJUMPER_2WAY_OPEN_NOPASTE";1;"";;;
34;"U6";"SOT23-5";1;"AP2112-3.3";;;
35;"D6,D5";"SOD-323";2;"3.6V";;;
36;"FB1";"0805-NO";1;"Ferrite";;;
37;"R14";"0603-NO";1;"4.7K";;;
38;"IC2";"LGA12_2X2MM";1;"MSA301";;;
39;"R10";"0603-NO";1;"2.2K";;;
40;"NEOPIX1,SENSE1";"JSTPH3";2;"JST PH 3";;;
41;"D3";"SOD-123";1;"MBR0540";;;
42;"U$63";"PQFN64-1";1;"ATSAMD51J19";;;
43;"SW1";"EG1390";1;"";;;
44;"R15";"RESPACK_4X0603";1;"100K";;;
45;"X2";"4UCONN_20329_V2";1;"microUSB";;;
46;"X4";"JSTPH2";1;"JSTPH";;;
47;"U$79";"PCBFEAT-REV-040";1;"";;;
48;"TFT1";"TFT_1.54IN_240X240_HANDSOLDER";1;"DISP_LCD_GENERIC_SPITFT_VDDIO_1.54_240X240_HANDSOLDER";;;
49;"U$2";"HALLOWINGM4_FRONT";1;"";;;

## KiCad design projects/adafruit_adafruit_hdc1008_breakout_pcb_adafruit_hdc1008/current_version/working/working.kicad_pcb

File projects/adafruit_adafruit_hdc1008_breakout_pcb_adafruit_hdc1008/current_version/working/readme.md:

# adafruit_hdc1008_breakout_pcb
 
## summary 
* id: adafruit_adafruit_hdc1008_breakout_pcb_adafruit_hdc1008
* user: adafruit
* name: adafruit_hdc1008_breakout_pcb
* board: adafruit_hdc1008
* repo: https://github.com/adafruit/Adafruit-HDC1008-Breakout-PCB

* src_file_repo_sch: 
* src_file_repo_sch_link: https://github.com/adafruit/Adafruit-HDC1008-Breakout-PCB/tree/master/
* full details link: https://github.com/oomlout/oomlout_oomp_project_bot_v_2/tree/main/projects/adafruit_adafruit_hdc1008_breakout_pcb_adafruit_hdc1008/current_version/working  

## schematic  
  
[schematic (pdf)](working_schematic.pdf) 

## pcb  

[board (pdf)](working.pdf)  

## working_bom
| Id | Designator | Footprint | Quantity | Designation | Supplier and ref |  | None | 
| --- | --- | --- | --- | --- | --- | --- | --- | 
| 1 | FID2,FID1 | FIDUCIAL_1MM | 2 | FIDUCIAL" |  |  | [''] | 
| 2 | U1 | DSBGA8_HDC1008 | 1 | HDC1008 |  |  | [''] | 
| 3 | U$2,U$3 | MOUNTINGHOLE_2.5_PLATED | 2 | MOUNTINGHOLE2.5 |  |  | [''] | 
| 4 | JP1 | 1X07_ROUND_70 | 1 |  |  |  | [''] | 
| 5 | R4,R3,R5,R1 | 0805-NO | 4 | 10K |  |  | [''] | 
| 6 | C1 | 0805-NO | 1 | 10uF |  |  | [''] | 
| 7 | R2 | _0805MP | 1 | 10K |  |  | [''] | 
| 8 | U$14 | ADAFRUIT_3.5MM | 1 |  |  |  | [''] | 

## bom_schematic
| Ref | Qnty | Value | Cmp name | Footprint | Description | Vendor | DNP | 
| --- | --- | --- | --- | --- | --- | --- | --- | 
| C1 | 1 | 10uF | CAP_CERAMIC0805-NOOUTLINE | working:0805-NO |  |  |  | 
| FID1, FID2 | 2 | FIDUCIAL"" | FIDUCIAL{dblquote}{dblquote} | working:FIDUCIAL_1MM |  |  |  | 
| JP1 | 1 | HEADER-1X770MIL | HEADER-1X770MIL | working:1X07_ROUND_70 |  |  |  | 
| R1, R3, R4, R5 | 4 | 10K | RESISTOR0805_NOOUTLINE | working:0805-NO |  |  |  | 
| R2 | 1 | 10K | RESISTOR_0805MP | working:_0805MP |  |  |  | 
| U1 | 1 | HDC1008 | HDC1008 | working:DSBGA8_HDC1008 |  |  |  | 
| U$2, U$3 | 2 | MOUNTINGHOLE2.5 | MOUNTINGHOLE2.5 | working:MOUNTINGHOLE_2.5_PLATED |  |  |  | 

## mounting_holes
| x | y | package | value | ref | size | 
| --- | --- | --- | --- | --- | --- | 
| 0.0 | 0.0 | MOUNTINGHOLE_2.5_PLATED | MOUNTINGHOLE2.5 | U$2 | m3 | 
| 12.7 | 0.0 | MOUNTINGHOLE_2.5_PLATED | MOUNTINGHOLE2.5 | U$3 | m3 |

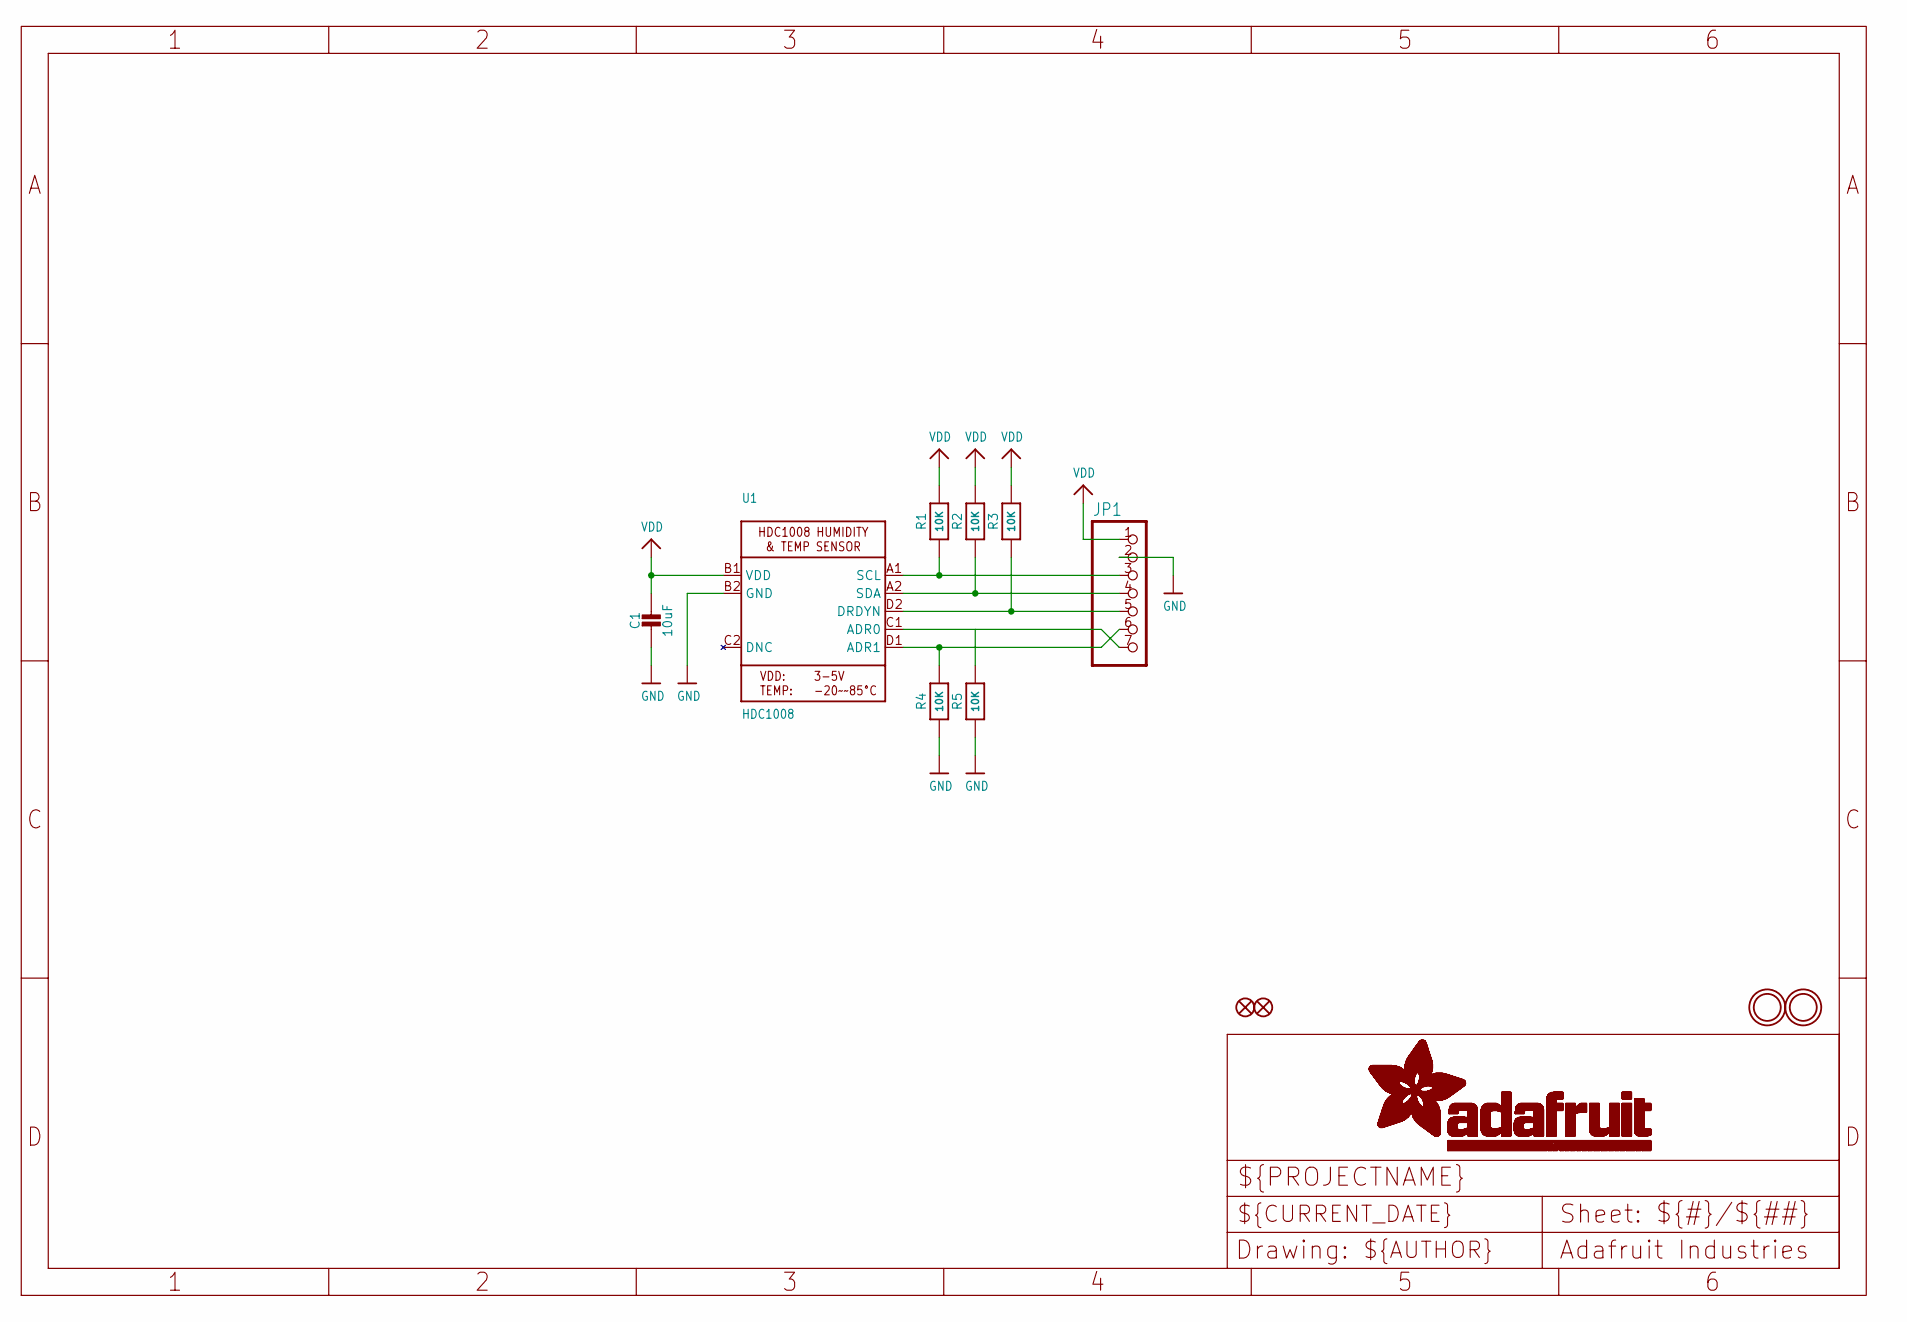
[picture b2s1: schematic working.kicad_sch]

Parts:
C1: 10uF; 0805-NO
FID1, FID2: FIDUCIAL""; FIDUCIAL_1MM
JP1: HEADER-1X770MIL; 1X07_ROUND_70
R1, R3, R4, R5: 10K; 0805-NO
R2: 10K; _0805MP
U1: HDC1008; DSBGA8_HDC1008
U$2, U$3: MOUNTINGHOLE2.5; MOUNTINGHOLE_2.5_PLATED

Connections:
A0: JP1.7, R5.2, U1.C1 (ADR0)
A1: JP1.6, R4.2, U1.D1 (ADR1)
GND: C1.2, JP1.2, R4.1, R5.1, U1.B2 (GND)
RDY: JP1.5, R3.1, U1.D2 (DRDYN)
SCL: JP1.3, R1.1, U1.A1 (SCL)
SDY: JP1.4, R2.1, U1.A2 (SDA)
VDD: C1.1, JP1.1, R1.2, R2.2, R3.2, U1.B1 (VDD)

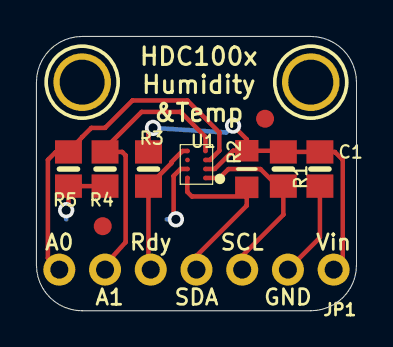
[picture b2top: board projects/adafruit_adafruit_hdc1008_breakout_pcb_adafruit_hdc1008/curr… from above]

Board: 2 copper layers, 17.8 x 15.2 mm, 13 parts (1 on the bottom side), 7 nets.

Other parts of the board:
U$14: ADAFRUIT_3.5MM

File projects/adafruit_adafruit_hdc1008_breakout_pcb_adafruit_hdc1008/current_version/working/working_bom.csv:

"Id";"Designator";"Footprint";"Quantity";"Designation";"Supplier and ref";
1;"FID2,FID1";"FIDUCIAL_1MM";2;"FIDUCIAL""";;;
2;"U1";"DSBGA8_HDC1008";1;"HDC1008";;;
3;"U$2,U$3";"MOUNTINGHOLE_2.5_PLATED";2;"MOUNTINGHOLE2.5";;;
4;"JP1";"1X07_ROUND_70";1;"";;;
5;"R4,R3,R5,R1";"0805-NO";4;"10K";;;
6;"C1";"0805-NO";1;"10uF";;;
7;"R2";"_0805MP";1;"10K";;;
8;"U$14";"ADAFRUIT_3.5MM";1;"";;;

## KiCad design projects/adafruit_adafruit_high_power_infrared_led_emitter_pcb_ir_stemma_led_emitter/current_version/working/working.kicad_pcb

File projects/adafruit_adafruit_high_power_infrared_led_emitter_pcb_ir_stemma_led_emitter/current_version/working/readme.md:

# adafruit_high_power_infrared_led_emitter_pcb
 
## summary 
* id: adafruit_adafruit_high_power_infrared_led_emitter_pcb_ir_stemma_led_emitter
* user: adafruit
* name: adafruit_high_power_infrared_led_emitter_pcb
* board: ir_stemma_led_emitter
* repo: https://github.com/adafruit/Adafruit-High-Power-Infrared-LED-Emitter-PCB

* src_file_repo_sch: 
* src_file_repo_sch_link: https://github.com/adafruit/Adafruit-High-Power-Infrared-LED-Emitter-PCB/tree/main/
* full details link: https://github.com/oomlout/oomlout_oomp_project_bot_v_2/tree/main/projects/adafruit_adafruit_high_power_infrared_led_emitter_pcb_ir_stemma_led_emitter/current_version/working  

## schematic  
  
[schematic (pdf)](working_schematic.pdf) 

## pcb  

[board (pdf)](working.pdf)  

## working_bom
| Id | Designator | Footprint | Quantity | Designation | Supplier and ref |  | None | 
| --- | --- | --- | --- | --- | --- | --- | --- | 
| 1 | Q1 | SOT23-WIDE | 1 | AO3406 |  |  | [''] | 
| 2 | FID3,FID2 | FIDUCIAL_1MM | 2 | FIDUCIAL_1MM |  |  | [''] | 
| 3 | PLABEL1 | PLABEL1 | 1 |  |  |  | [''] | 
| 4 | D3 | CHIPLED_1206 | 1 | 1206 IR 940nm |  |  | [''] | 
| 5 | PLABEL2 | PLABEL2 | 1 |  |  |  | [''] | 
| 6 | X4 | JSTPH3 | 1 | JST PH 3 |  |  | [''] | 
| 7 | R6,R4,R5 | 0603-NO | 3 | 22 |  |  | [''] | 
| 8 | R1,R2 | 0603-NO | 2 | 10K |  |  | [''] | 
| 9 | D4 | LED_1206_SIDE | 1 | 1206 IR 940nm Side |  |  | [''] | 
| 10 | PLABEL3 | PLABEL3 | 1 |  |  |  | [''] | 
| 11 | D1 | CHIPLED_0603_NOOUTLINE | 1 | RED |  |  | [''] | 
| 12 | C1 | 0805-NO | 1 | 10uF |  |  | [''] | 
| 13 | PLABEL0 | PLABEL0 | 1 |  |  |  | [''] | 
| 14 | U$1,U$8 | MOUNTINGHOLE_2.5_PLATED | 2 | MOUNTINGHOLE2.5 |  |  | [''] | 
| 15 | U$5 | PCBFEAT-REV-040 | 1 |  |  |  | [''] | 
| 16 | D2 | CHIPLED_0603_NOOUTLINE | 1 | GREEN |  |  | [''] | 
| 17 | JP1 | 1X03_OVAL | 1 | 0.1 Header" |  |  | [''] | 
| 18 | R3 | 0603-NO | 1 | 33K |  |  | [''] | 
| 19 | JP2 | 1X03_ROUND | 1 | 0.1 Header" |  |  | [''] | 
| 20 | U$10 | ADAFRUIT_3.5MM | 1 |  |  |  | [''] | 
| 21 | PLABEL11 | PLABEL11 | 1 |  |  |  | [''] | 
| 22 | PLABEL13 | PLABEL13 | 1 |  |  |  | [''] | 
| 23 | SJ1,SJ2 | SOLDERJUMPER_CLOSEDWIRE | 2 |  |  |  | [''] | 
| 24 | PLABEL6 | PLABEL6 | 1 |  |  |  | [''] | 
| 25 | PLABEL9 | PLABEL9 | 1 |  |  |  | [''] | 
| 26 | LED1 | LED5MM | 1 | 5mm |  |  | [''] | 
| 27 | PLABEL7 | PLABEL7 | 1 |  |  |  | [''] | 
| 28 | PLABEL5 | PLABEL5 | 1 |  |  |  | [''] | 
| 29 | PLABEL4 | PLABEL4 | 1 |  |  |  | [''] | 
| 30 | PLABEL8 | PLABEL8 | 1 |  |  |  | [''] | 
| 31 | PLABEL10 | PLABEL10 | 1 |  |  |  | [''] | 
| 32 | PLABEL14 | PLABEL14 | 1 |  |  |  | [''] | 
| 33 | PLABEL00 | PLABEL00 | 1 |  |  |  | [''] | 

## bom_schematic
| Ref | Qnty | Value | Cmp name | Footprint | Description | Vendor | DNP | 
| --- | --- | --- | --- | --- | --- | --- | --- | 
| C1 | 1 | 10uF | CAP_CERAMIC0805-NOOUTLINE | working:0805-NO |  |  |  | 
| D1 | 1 | RED | LED0603_NOOUTLINE | working:CHIPLED_0603_NOOUTLINE |  |  |  | 
| D2 | 1 | GREEN | LED0603_NOOUTLINE | working:CHIPLED_0603_NOOUTLINE |  |  |  | 
| D3 | 1 | 1206 IR 940nm | LED1206 | working:CHIPLED_1206 |  |  |  | 
| D4 | 1 | 1206 IR 940nm Side | LED_1206RA | working:LED_1206_SIDE |  |  |  | 
| FID2, FID3 | 2 | FIDUCIAL_1MM | FIDUCIAL_1MM | working:FIDUCIAL_1MM |  |  |  | 
| JP1 | 1 | 0.1" Header | HEADER-1X3 | working:1X03_OVAL |  |  |  | 
| JP2 | 1 | 0.1" Header | HEADER-1X3ROUND | working:1X03_ROUND |  |  |  | 
| LED1 | 1 | 5mm | LED5MM | working:LED5MM |  |  |  | 
| Q1 | 1 | AO3406 | MOSFET-NWIDE | working:SOT23-WIDE |  |  |  | 
| R1, R2 | 2 | 10K | RESISTOR_0603_NOOUT | working:0603-NO |  |  |  | 
| R3 | 1 | 33K | RESISTOR_0603_NOOUT | working:0603-NO |  |  |  | 
| R4, R5, R6 | 3 | 22 | RESISTOR_0603_NOOUT | working:0603-NO |  |  |  | 
| SJ1, SJ2 | 2 | SOLDERJUMPER_CLOSED | SOLDERJUMPER_CLOSED | working:SOLDERJUMPER_CLOSEDWIRE |  |  |  | 
| U$1, U$8 | 2 | MOUNTINGHOLE2.5 | MOUNTINGHOLE2.5 | working:MOUNTINGHOLE_2.5_PLATED |  |  |  | 
| X4 | 1 | JST PH 3 | CON_JST_PH_3PIN | working:JSTPH3 |  |  |  | 

## mounting_holes
| x | y | package | value | ref | size | 
| --- | --- | --- | --- | --- | --- | 
| 0.0 | 0.0 | MOUNTINGHOLE_2.5_PLATED | MOUNTINGHOLE2.5 | U$1 | m3 | 
| 0.0 | 12.7 | MOUNTINGHOLE_2.5_PLATED | MOUNTINGHOLE2.5 | U$8 | m3 |

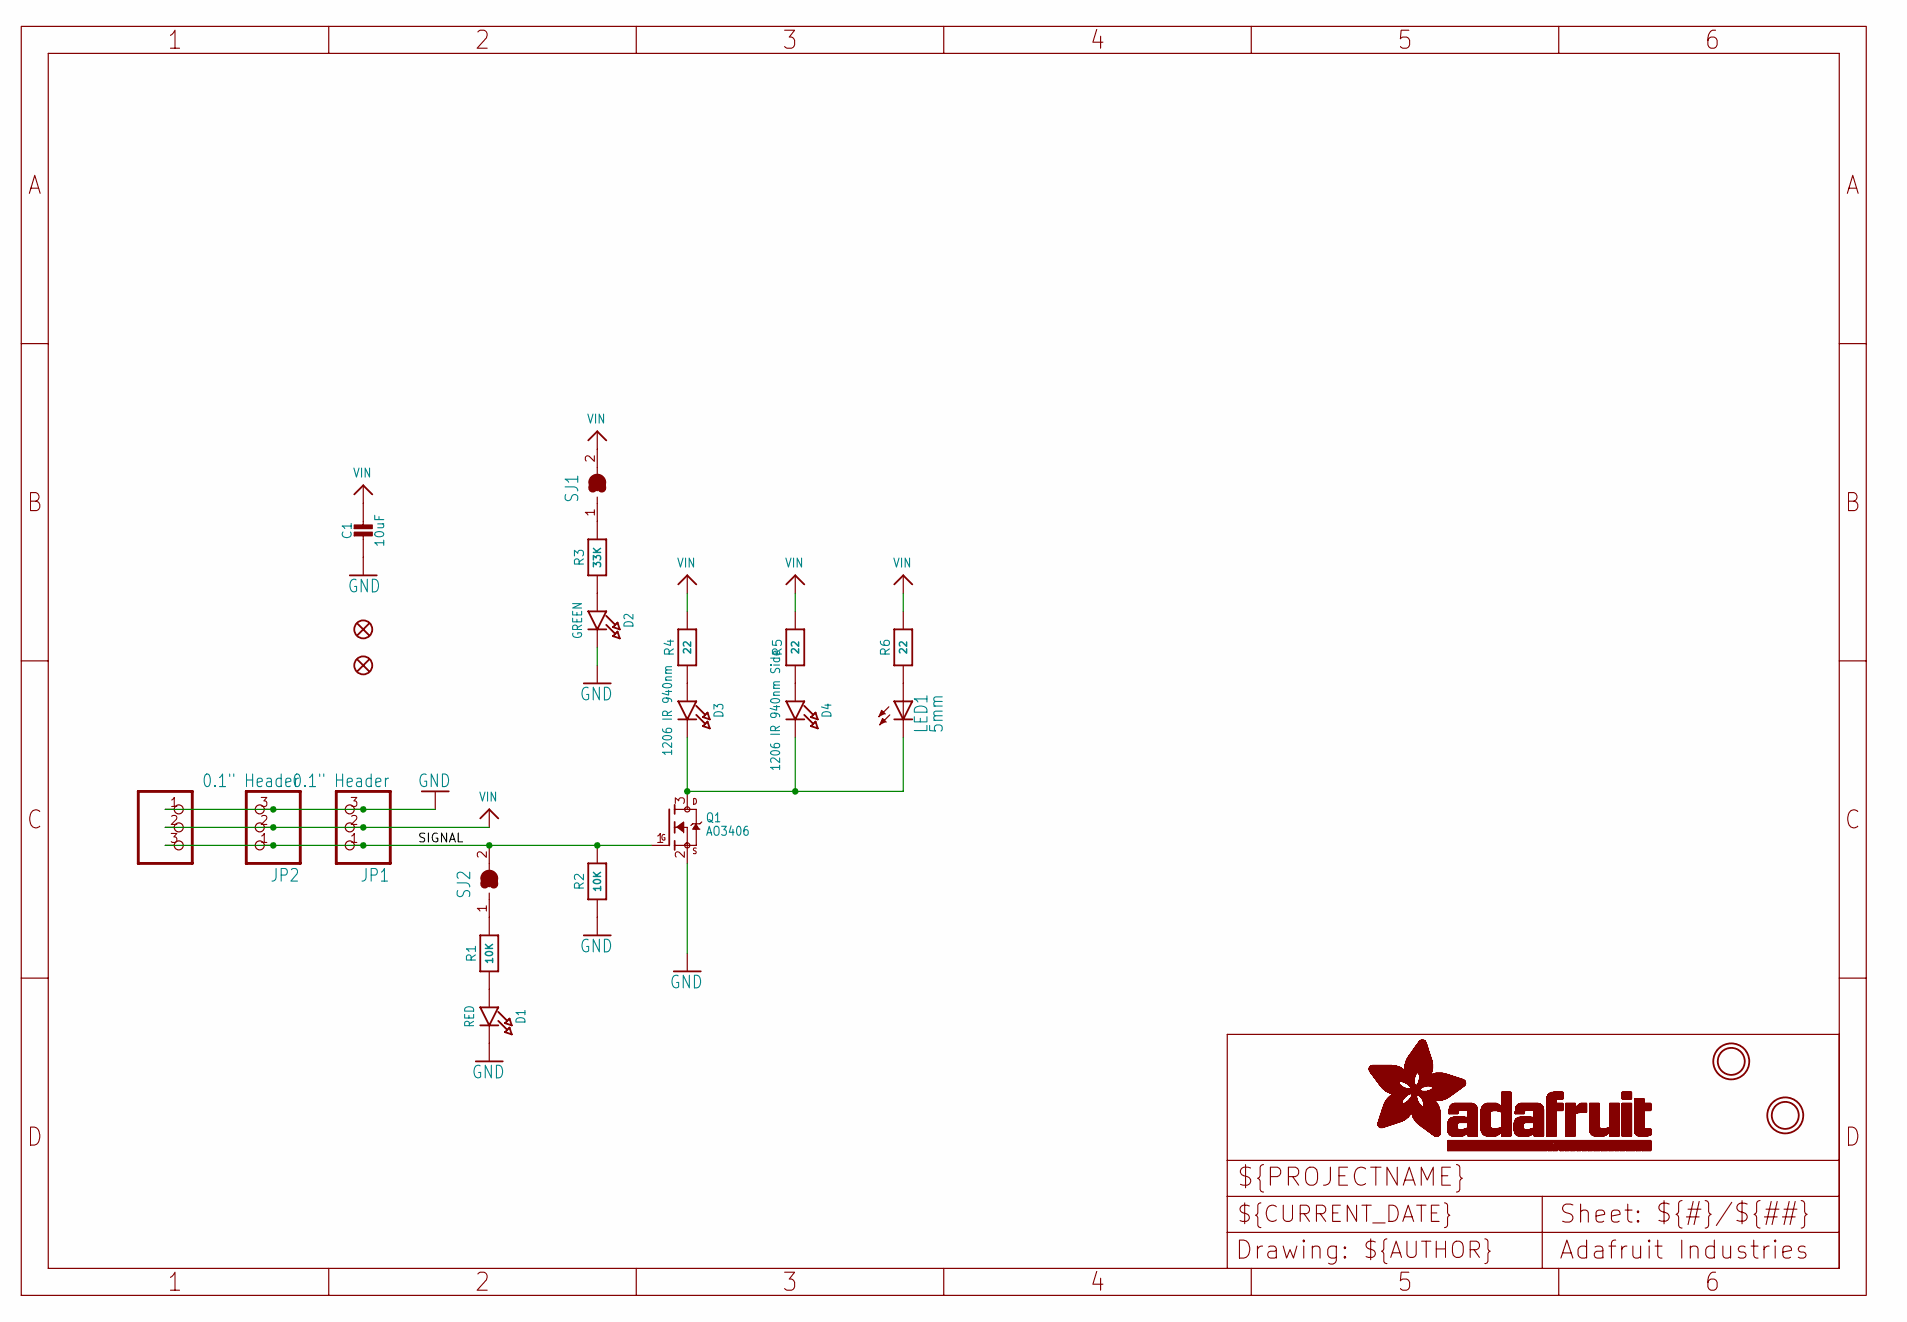
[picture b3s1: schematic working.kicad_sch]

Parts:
C1: 10uF; 0805-NO
D1: RED; CHIPLED_0603_NOOUTLINE
D2: GREEN; CHIPLED_0603_NOOUTLINE
D3: 1206 IR 940nm; CHIPLED_1206
D4: 1206 IR 940nm Side; LED_1206_SIDE
FID2, FID3: FIDUCIAL_1MM
JP1: 0.1" Header; 1X03_OVAL
JP2: 0.1" Header; 1X03_ROUND
LED1: 5mm; LED5MM
Q1: AO3406; SOT23-WIDE
R1, R2: 10K; 0603-NO
R3: 33K; 0603-NO
R4, R5, R6: 22; 0603-NO
SJ1, SJ2: SOLDERJUMPER_CLOSED; SOLDERJUMPER_CLOSEDWIRE
U$1, U$8: MOUNTINGHOLE2.5; MOUNTINGHOLE_2.5_PLATED
X4: JST PH 3; JSTPH3

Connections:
GND: C1.2, D1.C, D2.C, JP1.3, JP2.3, Q1.2 (S), R2.1, X4.1
unnamed: R3.2, SJ1.1
unnamed: D1.A, R1.1
unnamed: R1.2, SJ2.1
unnamed: D3.C, D4.C, LED1.K (C), Q1.3 (D)
unnamed: D3.A, R4.1
unnamed: D4.A, R5.1
unnamed: LED1.A, R6.1
unnamed: D2.A, R3.1
SIGNAL: JP1.1, JP2.1, Q1.1 (G), R2.2, SJ2.2, X4.3
VIN: C1.1, JP1.2, JP2.2, R4.2, R5.2, R6.2, SJ1.2, X4.2
